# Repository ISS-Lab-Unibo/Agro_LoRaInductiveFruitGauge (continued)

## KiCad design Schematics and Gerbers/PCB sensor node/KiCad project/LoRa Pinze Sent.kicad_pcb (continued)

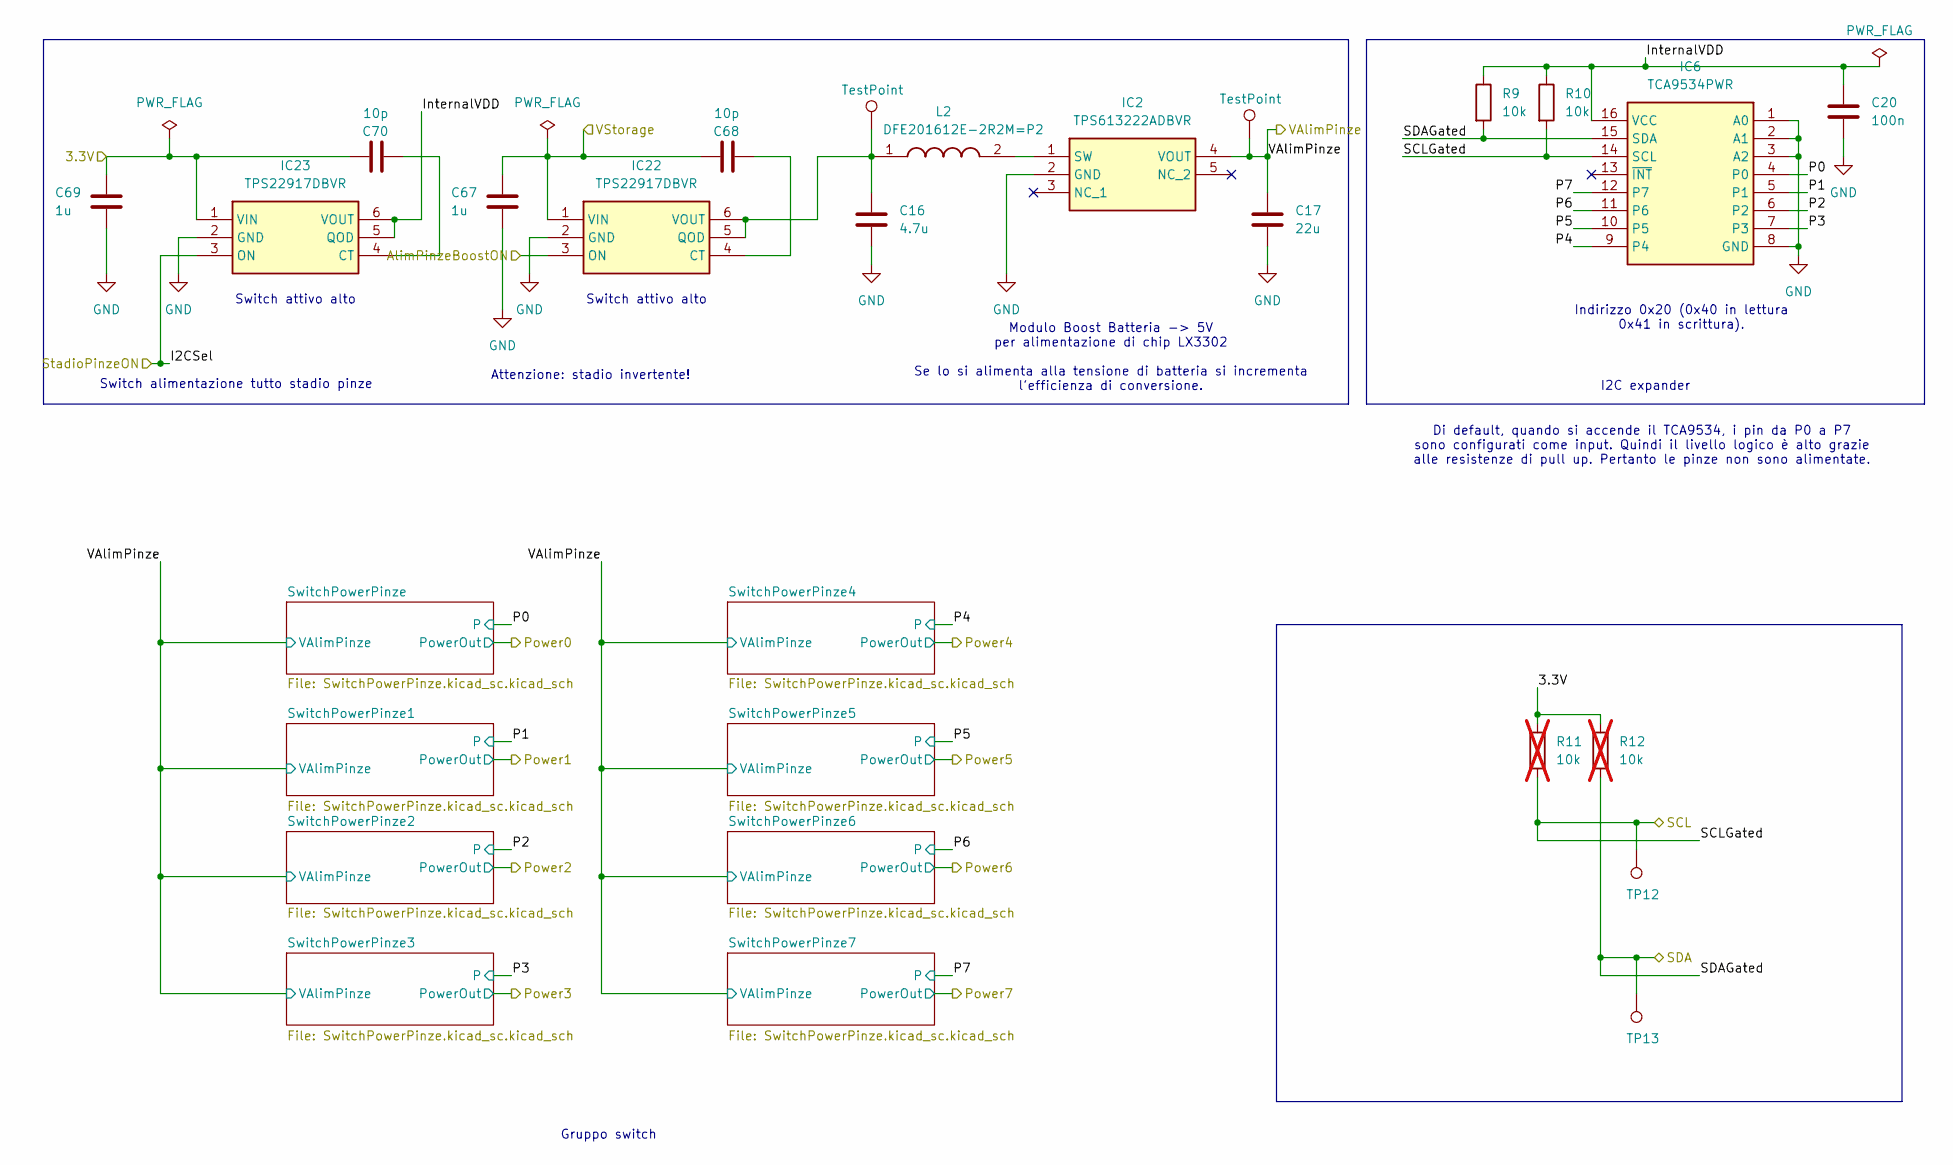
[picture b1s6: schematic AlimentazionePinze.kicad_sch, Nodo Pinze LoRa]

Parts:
C16: 4.7u; C_0402_1005Metric_Pad0.74x0.62mm_HandSolder; LCSC C23733
C17: 22u; C_0805_2012Metric_Pad1.18x1.45mm_HandSolder; LCSC C45783
C20: 100n; C_0402_1005Metric_Pad0.74x0.62mm_HandSolder; LCSC C1525
C67, C69: 1u; C_0402_1005Metric_Pad0.74x0.62mm_HandSolder; LCSC C52923
C68, C70: 10p; C_0402_1005Metric_Pad0.74x0.62mm_HandSolder; LCSC C32949
IC2: TPS613222ADBVR; SOT95P280X145-5N; Manufacturer_Part_Number TPS613222ADBVR; Mouser Part Number 595-TPS613222ADBVR
IC6: TCA9534PWR; SOP65P640X120-16N; Manufacturer_Part_Number TCA9534PWR; Mouser Part Number 595-TCA9534PWR
IC22, IC23: TPS22917DBVR; SOT95P280X145-6N; Manufacturer_Part_Number TPS22917DBVR; Mouser Part Number 595-TPS22917DBVR
L2: DFE201612E-2R2M=P2; 1286ASH1R0MP2; Manufacturer_Part_Number DFE201612E-2R2M=P2; Mouser Part Number 81-DFE201612E-2R2MP2
R9, R10: 10k; R_0402_1005Metric; LCSC C25744
R11, R12: 10k; R_0402_1005Metric; LCSC C25744; not fitted
TP10, TP11, TP12, TP13: TestPoint; TestPoint_Pad_1.0x1.0mm

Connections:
/+5V: C17.1, IC2.4 (VOUT), TP11.1 (1_1); also elsewhere on the board
/AlimentazionePinze/InternalVDD: C20.1, IC6.16 (VCC), IC23.5 (QOD), IC23.6 (VOUT), R9.1, R10.1
/AlimentazionePinze/P0: IC6.4 (P0); also elsewhere on the board
/AlimentazionePinze/P1: IC6.5 (P1); also elsewhere on the board
/AlimentazionePinze/P2: IC6.6 (P2); also elsewhere on the board
/AlimentazionePinze/P3: IC6.7 (P3); also elsewhere on the board
/AlimentazionePinze/P4: IC6.9 (P4); also elsewhere on the board
/AlimentazionePinze/P5: IC6.10 (P5); also elsewhere on the board
/AlimentazionePinze/P6: IC6.11 (P6); also elsewhere on the board
/AlimentazionePinze/P7: IC6.12 (P7); also elsewhere on the board
/BoostOnPinze: IC22.3 (ON); also elsewhere on the board
/I2C1_SCL_PA12: IC6.14 (SCL), R10.2, R11.2, TP12.1 (1_1); also elsewhere on the board
/I2C1_SDA_PA11: IC6.15 (SDA), R9.2, R12.2, TP13.1 (1_1); also elsewhere on the board
/PinzeOn: IC23.3 (ON); also elsewhere on the board
/VBattery: C67.1, C68.1, IC22.1 (VIN); also elsewhere on the board
GND: C16.2, C17.2, C20.2, C67.2, C69.2, IC2.2 (GND), IC6.1 (A0), IC6.2 (A1), IC6.3 (A2), IC6.8 (GND), IC22.2 (GND), IC23.2 (GND); also elsewhere on the board
unnamed: IC2.1 (SW), L2.2
unnamed: C68.2, IC22.4 (CT)
unnamed: C16.1, IC22.5 (QOD), IC22.6 (VOUT), L2.1, TP10.1 (1_1)
unnamed: C70.2, IC23.4 (CT)
VDD_MCU_LRA: C69.1, C70.1, IC23.1 (VIN), R11.1, R12.1; also elsewhere on the board

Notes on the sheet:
Attenzione: stadio invertente!
Modulo Boost Batteria -> 5V per alimentazione di chip LX3302 Se lo si alimenta alla tensione di batteria si incrementa l'efficienza di conversione.
Gruppo switch
Di default, quando si accende il TCA9534, i pin da P0 a P7 sono configurati come input. Quindi il livello logico è alto grazie alle resistenze di pull up. Pertanto le pinze non sono alimentate.
Switch attivo alto
I2C expander
Indirizzo 0x20 (0x40 in lettura 0x41 in scrittura).
Switch alimentazione tutto stadio pinze

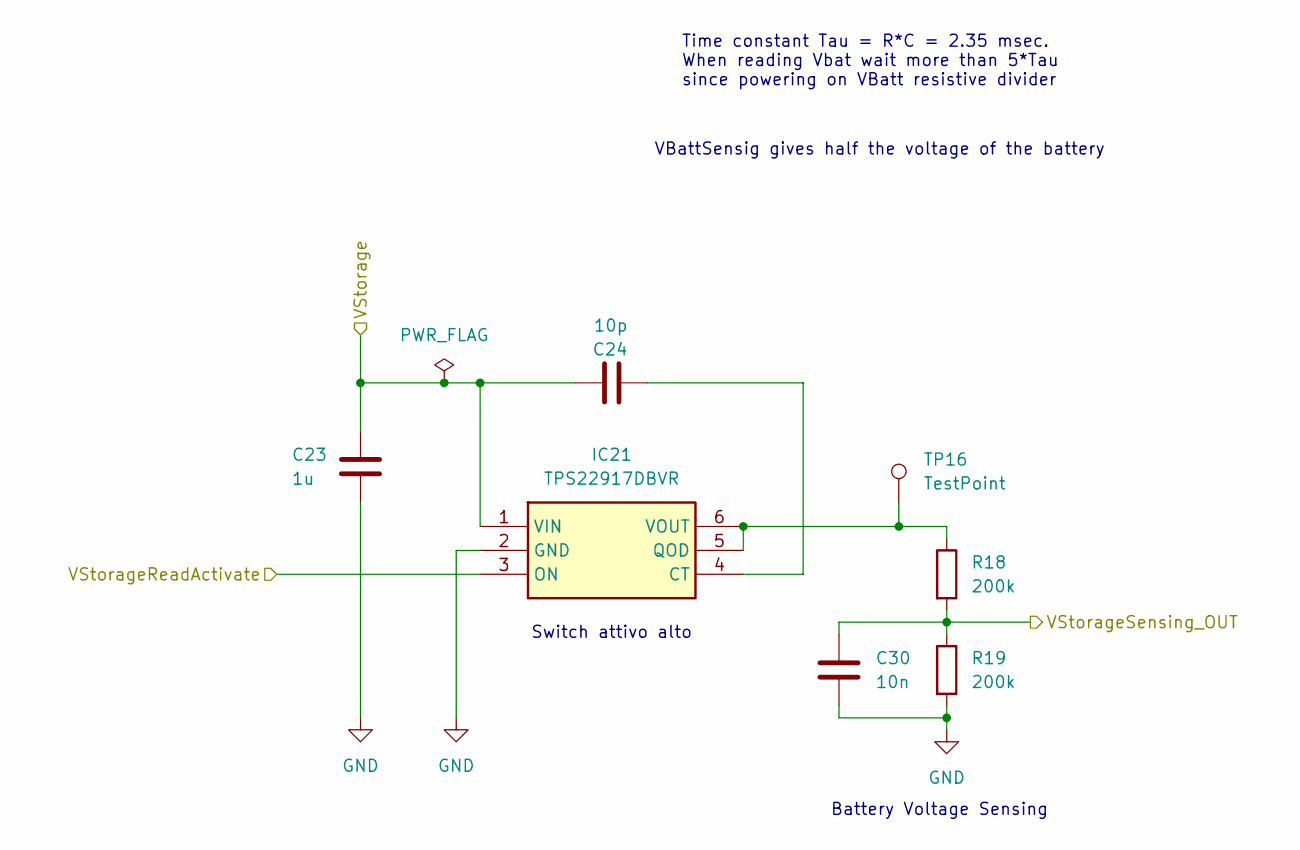
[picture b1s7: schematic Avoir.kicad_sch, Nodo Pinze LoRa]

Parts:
C23: 1u; C_0402_1005Metric_Pad0.74x0.62mm_HandSolder; LCSC C52923
C24: 10p; C_0402_1005Metric_Pad0.74x0.62mm_HandSolder; LCSC C32949
C30: 10n; C_0402_1005Metric_Pad0.74x0.62mm_HandSolder; LCSC C15195
IC21: TPS22917DBVR; SOT95P280X145-6N; Manufacturer_Part_Number TPS22917DBVR; Mouser Part Number 595-TPS22917DBVR
R18, R19: 200k; R_0402_1005Metric; LCSC C25764
TP16: TestPoint; TestPoint_Pad_1.0x1.0mm

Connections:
/VBattery: C23.1, C24.1, IC21.1 (VIN); also elsewhere on the board
/VStorageReadActivate: IC21.3 (ON); also elsewhere on the board
/VStorageSensing: C30.1, R18.2, R19.1; also elsewhere on the board
GND: C23.2, C30.2, IC21.2 (GND), R19.2; also elsewhere on the board
unnamed: C24.2, IC21.4 (CT)
unnamed: IC21.5 (QOD), IC21.6 (VOUT), R18.1, TP16.1 (1_1)

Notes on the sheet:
Time constant Tau = R*C = 2.35 msec. When reading Vbat wait more than 5*Tau since powering on VBatt resistive divider
VBattSensig gives half the voltage of the battery
Switch attivo alto
Battery Voltage Sensing

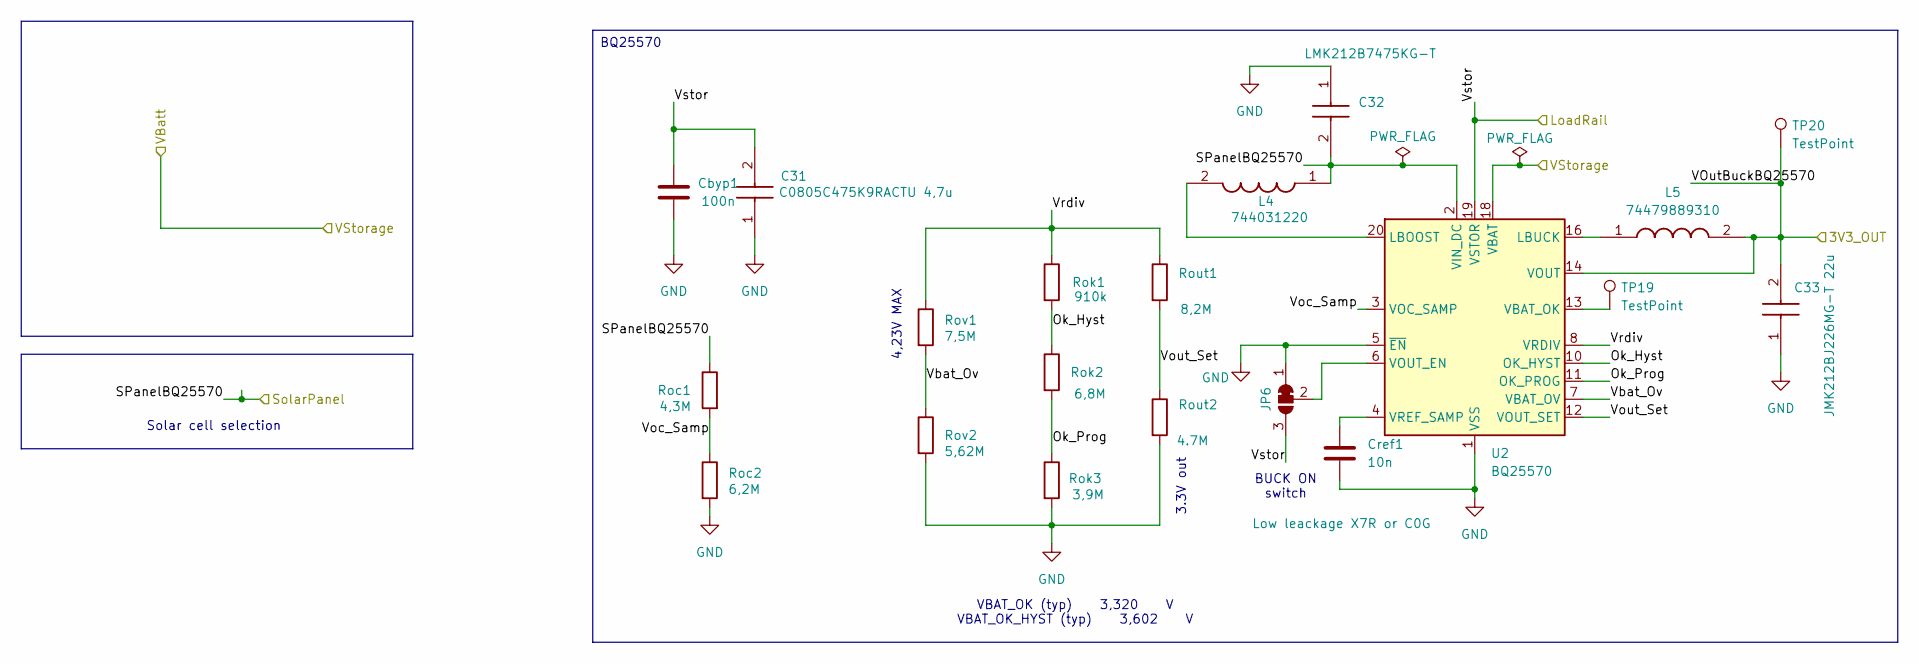
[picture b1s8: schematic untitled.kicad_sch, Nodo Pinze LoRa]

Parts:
C31: C0805C475K9RACTU 4,7u; C0805; Manufacturer_Part_Number C0805C475K9RACTU; Mouser Part Number 80-C0805C475K9R
C32: LMK212B7475KG-T; CAPC2012X135N; Manufacturer_Part_Number LMK212B7475KG-T; Mouser Part Number 963-LMK212B7475KG-T
C33: JMK212BJ226MG-T 22u; CAPC2013X135N; Manufacturer_Part_Number JMK212BJ226MG-T; Mouser Part Number 963-JMK212BJ226MG-T
Cbyp1: 100n; C_0402_1005Metric_Pad0.74x0.62mm_HandSolder; LCSC C1525
Cref1: 10n; C_0402_1005Metric_Pad0.74x0.62mm_HandSolder; LCSC C15195
JP6: SolderJumper_3_Bridged12; SolderJumper-3_P1.3mm_Bridged12_RoundedPad1.0x1.5mm_NumberL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
L4: 744031220; WE-TPC_381692; Manufacturer_Part_Number 744031220; Mouser Part Number 710-744031220
L5: 74479889310; INDC2521X120N; Manufacturer_Part_Number 74479889310; LCSC C191565
Roc1: 4,3M; R_0402_1005Metric_Pad0.72x0.64mm_HandSolder; LCSC C327242
Roc2: 6,2M; R_0402_1005Metric_Pad0.72x0.64mm_HandSolder; LCSC C159000
Rok1: 910k; R_0402_1005Metric_Pad0.72x0.64mm_HandSolder; LCSC C324817
Rok2: 6,8M; R_0402_1005Metric_Pad0.72x0.64mm_HandSolder; LCSC C620473
Rok3: 3,9M; R_0402_1005Metric_Pad0.72x0.64mm_HandSolder; LCSC C30329
Rout1: 8,2M; R_0402_1005Metric_Pad0.72x0.64mm_HandSolder; LCSC C172186
Rout2: 4.7M; R_0402_1005Metric_Pad0.72x0.64mm_HandSolder; LCSC C49654986
Rov1: 7,5M; R_0402_1005Metric_Pad0.72x0.64mm_HandSolder; LCSC C137839
Rov2: 5,62M; R_0402_1005Metric_Pad0.72x0.64mm_HandSolder; LCSC C2929925
TP19, TP20: TestPoint; TestPoint_Pad_1.0x1.0mm
U2: BQ25570; QFN-20-1EP_3.5x3.5mm_P0.5mm_EP2x2mm; LCSC C506250

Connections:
/LoadRail: C31.2, Cbyp1.2, JP6.3 (B), U2.19 (VSTOR)
/SolarPanel: C32.2, L4.1, Roc1.1, U2.2 (VIN_DC); also elsewhere on the board
/VBattery: U2.18 (VBAT); also elsewhere on the board
/power_supply1/Ok_Hyst: Rok1.2, Rok2.1, U2.10 (OK_HYST)
/power_supply1/Ok_Prog: Rok2.2, Rok3.1, U2.11 (OK_PROG)
/power_supply1/Vbat_Ov: Rov1.2, Rov2.1, U2.7 (VBAT_OV)
/power_supply1/Voc_Samp: Roc1.2, Roc2.1, U2.3 (VOC_SAMP)
/power_supply1/Vout_Set: Rout1.2, Rout2.1, U2.12 (VOUT_SET)
/power_supply1/Vrdiv: Rok1.1, Rout1.1, Rov1.1, U2.8 (VRDIV)
GND: C31.1, C32.1, C33.1, Cbyp1.1, Cref1.1, JP6.1 (A), Roc2.2, Rok3.2, Rout2.2, Rov2.2, U2.1 (VSS), U2.5 (~EN), U2.9 (VSS), U2.15 (VSS), U2.17 (VSS), U2.21 (VSS); also elsewhere on the board
unnamed: JP6.2 (C), U2.6 (VOUT_EN)
unnamed: L4.2, U2.20 (LBOOST)
unnamed: L5.1, U2.16 (LBUCK)
unnamed: TP19.1 (1_1), U2.13 (VBAT_OK)
unnamed: Cref1.2, U2.4 (VREF_SAMP)
VDD_MCU_LRA: C33.2, L5.2, TP20.1 (1_1), U2.14 (VOUT); also elsewhere on the board

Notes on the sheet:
BUCK ON switch
3.3V out
4,23V MAX
Solar cell selection
VBAT_OK (typ) 3,320 V VBAT_OK_HYST (typ) 3,602 V
BQ25570

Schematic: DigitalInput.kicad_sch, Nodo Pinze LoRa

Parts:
D21, D29: BAV199; SOT95P230X100-3N; Manufacturer_Part_Number BAV199; Mouser Part Number N/A
J9: 53398-0471; 533980471; Manufacturer_Part_Number 53398-0471; Mouser Part Number 538-53398-0471
R47, R49: 12k; R_0402_1005Metric; LCSC C25752
R48, R50: 22k; R_0402_1005Metric; LCSC C25768

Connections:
/+5V: D21.2 (CATHODE), D29.2 (CATHODE); also elsewhere on the board
/AlimentazionePinze/Power0: J9.4; also elsewhere on the board
/DigitalInputMux/D0: R47.1, R48.2; also elsewhere on the board
/DigitalInputMux/DigitalInput/IND: D21.3 (COMMON), J9.3, R47.2
/DigitalInputMux/DigitalInput/INT: D29.3 (COMMON), J9.2, R49.2
/DigitalInputMux/T0: R49.1, R50.2; also elsewhere on the board
GND: D21.1 (ANODE), D29.1 (ANODE), J9.1, R48.1, R50.1; also elsewhere on the board

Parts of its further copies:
D22, D23, D24, D25, D26, D27, D28, D30, D31, D32, D33, D34, D35, D36: BAV199; SOT95P230X100-3N; Manufacturer_Part_Number BAV199; Mouser Part Number N/A
J10, J11, J12, J13, J14, J15, J16: 53398-0471; 533980471; Manufacturer_Part_Number 53398-0471; Mouser Part Number 538-53398-0471
R51, R53, R55, R57, R59, R61, R63, R65, R67, R69, R71, R73, R75, R77: 12k; R_0402_1005Metric; LCSC C25752
R52, R54, R56, R58, R60, R62, R64, R66, R68, R70, R72, R74, R76, R78: 22k; R_0402_1005Metric; LCSC C25768

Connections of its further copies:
/+5V: D22.2 (CATHODE), D23.2 (CATHODE), D24.2 (CATHODE), D25.2 (CATHODE), D26.2 (CATHODE), D27.2 (CATHODE), D28.2 (CATHODE), D30.2 (CATHODE), D31.2 (CATHODE), D32.2 (CATHODE), D33.2 (CATHODE), D34.2 (CATHODE), D35.2 (CATHODE), D36.2 (CATHODE); also elsewhere on the board
/AlimentazionePinze/Power1: J10.4; also elsewhere on the board
/AlimentazionePinze/Power2: J11.4; also elsewhere on the board
/AlimentazionePinze/Power3: J12.4; also elsewhere on the board
/AlimentazionePinze/Power4: J13.4; also elsewhere on the board
/AlimentazionePinze/Power5: J14.4; also elsewhere on the board
/AlimentazionePinze/Power6: J15.4; also elsewhere on the board
/AlimentazionePinze/Power7: J16.4; also elsewhere on the board
/DigitalInputMux/D1: R51.1, R52.2; also elsewhere on the board
/DigitalInputMux/D2: R55.1, R56.2; also elsewhere on the board
/DigitalInputMux/D3: R59.1, R60.2; also elsewhere on the board
/DigitalInputMux/D4: R63.1, R64.2; also elsewhere on the board
/DigitalInputMux/D5: R67.1, R68.2; also elsewhere on the board
/DigitalInputMux/D6: R71.1, R72.2; also elsewhere on the board
/DigitalInputMux/D7: R75.1, R76.2; also elsewhere on the board
/DigitalInputMux/DigitalInput1/IND: D22.3 (COMMON), J10.3, R51.2
/DigitalInputMux/DigitalInput1/INT: D30.3 (COMMON), J10.2, R53.2
/DigitalInputMux/DigitalInput2/IND: D23.3 (COMMON), J11.3, R55.2
/DigitalInputMux/DigitalInput2/INT: D31.3 (COMMON), J11.2, R57.2
/DigitalInputMux/DigitalInput3/IND: D24.3 (COMMON), J12.3, R59.2
/DigitalInputMux/DigitalInput3/INT: D32.3 (COMMON), J12.2, R61.2
/DigitalInputMux/DigitalInput4/IND: D25.3 (COMMON), J13.3, R63.2
/DigitalInputMux/DigitalInput4/INT: D33.3 (COMMON), J13.2, R65.2
/DigitalInputMux/DigitalInput5/IND: D26.3 (COMMON), J14.3, R67.2
/DigitalInputMux/DigitalInput5/INT: D34.3 (COMMON), J14.2, R69.2
/DigitalInputMux/DigitalInput6/IND: D27.3 (COMMON), J15.3, R71.2
/DigitalInputMux/DigitalInput6/INT: D35.3 (COMMON), J15.2, R73.2
/DigitalInputMux/DigitalInput7/IND: D28.3 (COMMON), J16.3, R75.2
/DigitalInputMux/DigitalInput7/INT: D36.3 (COMMON), J16.2, R77.2
/DigitalInputMux/T1: R53.1, R54.2; also elsewhere on the board
/DigitalInputMux/T2: R57.1, R58.2; also elsewhere on the board
/DigitalInputMux/T3: R61.1, R62.2; also elsewhere on the board
/DigitalInputMux/T4: R65.1, R66.2; also elsewhere on the board
/DigitalInputMux/T5: R69.1, R70.2; also elsewhere on the board
/DigitalInputMux/T6: R73.1, R74.2; also elsewhere on the board
/DigitalInputMux/T7: R77.1, R78.2; also elsewhere on the board
GND: D22.1 (ANODE), D23.1 (ANODE), D24.1 (ANODE), D25.1 (ANODE), D26.1 (ANODE), D27.1 (ANODE), D28.1 (ANODE), D30.1 (ANODE), D31.1 (ANODE), D32.1 (ANODE), D33.1 (ANODE), D34.1 (ANODE), D35.1 (ANODE), D36.1 (ANODE), J10.1, J11.1, J12.1, J13.1, J14.1, J15.1, J16.1, R52.1, R54.1, R56.1, R58.1, R60.1, R62.1, R64.1, R66.1, R68.1, R70.1, R72.1, R74.1, R76.1, R78.1; also elsewhere on the board

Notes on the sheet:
Partitore resisttivo: entrano 5V, escono 3.23V

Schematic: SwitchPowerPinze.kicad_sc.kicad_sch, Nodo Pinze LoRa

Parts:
C43, C45: 1u; C_0402_1005Metric_Pad0.74x0.62mm_HandSolder; LCSC C52923
C44: 10p; C_0402_1005Metric_Pad0.74x0.62mm_HandSolder; LCSC C32949
IC13: TPS22917DBVR; SOT95P280X145-6N; Manufacturer_Part_Number TPS22917DBVR; Mouser Part Number 595-TPS22917DBVR

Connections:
/+5V: C43.1, C44.1, IC13.1 (VIN); also elsewhere on the board
/AlimentazionePinze/P0: IC13.3 (ON); also elsewhere on the board
/AlimentazionePinze/Power0: C45.1, IC13.5 (QOD), IC13.6 (VOUT); also elsewhere on the board
GND: C43.2, C45.2, IC13.2 (GND); also elsewhere on the board
unnamed: C44.2, IC13.4 (CT)

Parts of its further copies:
C46, C48, C49, C50, C52, C54, C55, C57, C58, C60, C61, C63, C64, C66, C71, C73: 1u; C_0402_1005Metric_Pad0.74x0.62mm_HandSolder; LCSC C52923
C47, C51, C53, C56, C59, C62, C65, C72: 10p; C_0402_1005Metric_Pad0.74x0.62mm_HandSolder; LCSC C32949
IC14, IC15, IC16, IC17, IC18, IC19, IC20, IC24: TPS22917DBVR; SOT95P280X145-6N; Manufacturer_Part_Number TPS22917DBVR; Mouser Part Number 595-TPS22917DBVR

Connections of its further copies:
/+5V: C46.1, C47.1, C49.1, C50.1, C51.1, C53.1, C55.1, C56.1, C58.1, C59.1, C61.1, C62.1, C64.1, C65.1, IC14.1 (VIN), IC15.1 (VIN), IC16.1 (VIN), IC17.1 (VIN), IC18.1 (VIN), IC19.1 (VIN), IC20.1 (VIN); also elsewhere on the board
/AlimentazionePinze/P1: IC14.3 (ON); also elsewhere on the board
/AlimentazionePinze/P2: IC15.3 (ON); also elsewhere on the board
/AlimentazionePinze/P3: IC16.3 (ON); also elsewhere on the board
/AlimentazionePinze/P4: IC17.3 (ON); also elsewhere on the board
/AlimentazionePinze/P5: IC18.3 (ON); also elsewhere on the board
/AlimentazionePinze/P6: IC19.3 (ON); also elsewhere on the board
/AlimentazionePinze/P7: IC20.3 (ON); also elsewhere on the board
/AlimentazionePinze/Power1: C48.1, IC14.5 (QOD), IC14.6 (VOUT); also elsewhere on the board
/AlimentazionePinze/Power2: C54.1, IC15.5 (QOD), IC15.6 (VOUT); also elsewhere on the board
/AlimentazionePinze/Power3: C57.1, IC16.5 (QOD), IC16.6 (VOUT); also elsewhere on the board
/AlimentazionePinze/Power4: C60.1, IC17.5 (QOD), IC17.6 (VOUT); also elsewhere on the board
/AlimentazionePinze/Power5: C63.1, IC18.5 (QOD), IC18.6 (VOUT); also elsewhere on the board
/AlimentazionePinze/Power6: C66.1, IC19.5 (QOD), IC19.6 (VOUT); also elsewhere on the board
/AlimentazionePinze/Power7: C52.1, IC20.5 (QOD), IC20.6 (VOUT); also elsewhere on the board
/AnalogPowerIN: IC24.3 (ON); also elsewhere on the board
/InputAnalogico/AnalogSupply: C73.1, IC24.5 (QOD), IC24.6 (VOUT); also elsewhere on the board
GND: C46.2, C48.2, C49.2, C50.2, C52.2, C54.2, C55.2, C57.2, C58.2, C60.2, C61.2, C63.2, C64.2, C66.2, C71.2, C73.2, IC14.2 (GND), IC15.2 (GND), IC16.2 (GND), IC17.2 (GND), IC18.2 (GND), IC19.2 (GND), IC20.2 (GND), IC24.2 (GND); also elsewhere on the board
unnamed: C47.2, IC14.4 (CT)
unnamed: C53.2, IC15.4 (CT)
unnamed: C56.2, IC16.4 (CT)
unnamed: C59.2, IC17.4 (CT)
unnamed: C62.2, IC18.4 (CT)
unnamed: C65.2, IC19.4 (CT)
unnamed: C51.2, IC20.4 (CT)
unnamed: C72.2, IC24.4 (CT)
VDD_MCU_LRA: C71.1, C72.1, IC24.1 (VIN); also elsewhere on the board

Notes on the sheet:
Switch attivo alto

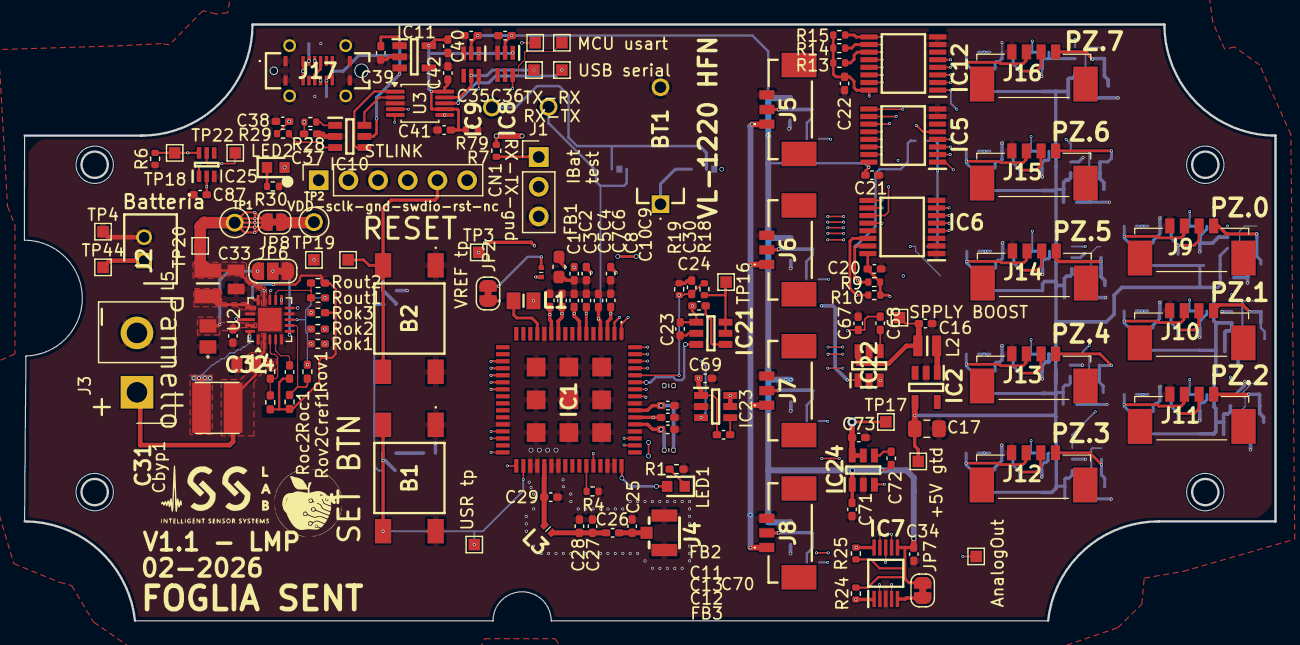
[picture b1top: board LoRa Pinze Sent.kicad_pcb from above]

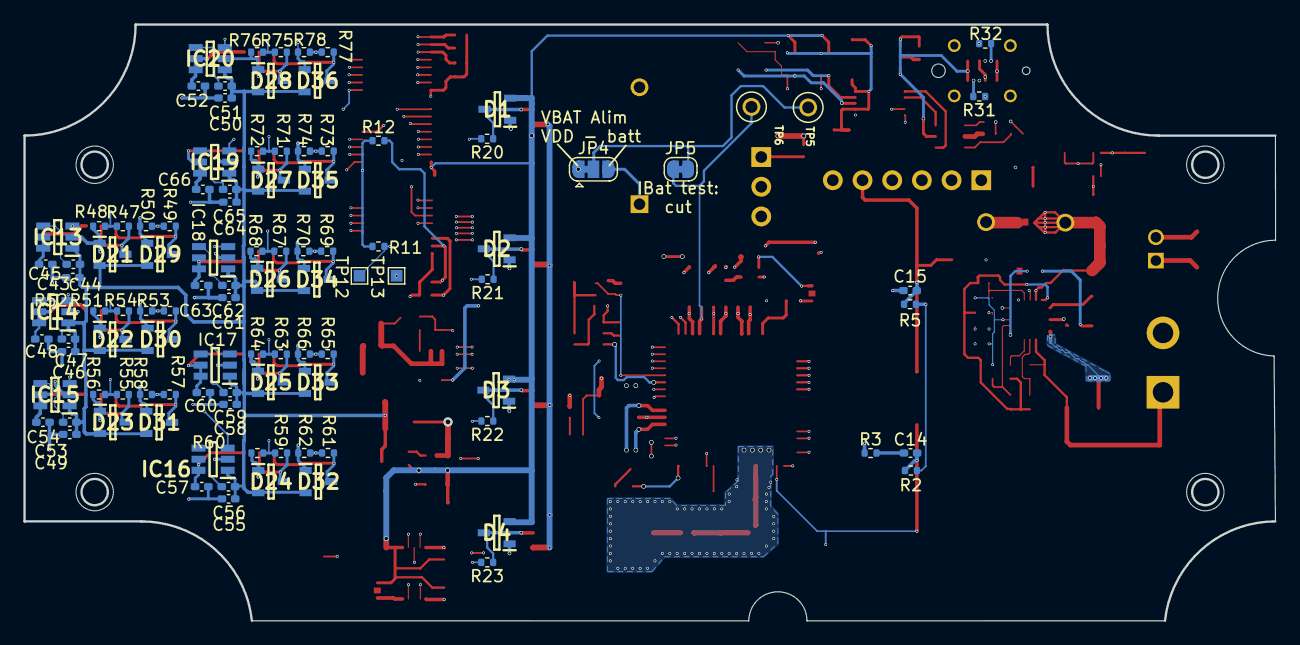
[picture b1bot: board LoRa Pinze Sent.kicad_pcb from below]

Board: 6 copper layers, 107.0 x 51.0 mm, 253 parts (103 on the bottom side), 146 nets.

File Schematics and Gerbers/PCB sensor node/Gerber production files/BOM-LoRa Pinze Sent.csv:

Comment,Designator,Footprint,LCSC,Quantity
0.47u,C2,C_0603_1608Metric_Pad1.08x0.95mm_HandSolder,C1623,1
10,"R20,R21,R22,R23",R_0402_1005Metric,C25077,4
100k,"R13,R14,R15,R24,R25",R_0402_1005Metric,C25741,5
100n,"C1,C10,C11,C15,C20,C21,C22,C3,C34,C35,C36,C41,C42,C5,C7,C87,Cbyp1",C_0402_1005Metric_Pad0.74x0.62mm_HandSolder,C1525,17
100p,C26,C_0402_1005Metric_Pad0.74x0.62mm_HandSolder,C1546,1
10k,"R10,R4,R5,R9",R_0402_1005Metric,C25744,4
10n,"C30,Cref1",C_0402_1005Metric_Pad0.74x0.62mm_HandSolder,C15195,2
10p,"C24,C37,C38,C44,C47,C51,C53,C56,C59,C62,C65,C68,C70,C72",C_0402_1005Metric_Pad0.74x0.62mm_HandSolder,C32949,14
12k,"R47,R49,R51,R53,R55,R57,R59,R61,R63,R65,R67,R69,R71,R73,R75,R77",R_0402_1005Metric,C25752,16
1k,R79,R_0402_1005Metric,C11702,1
1u,"C12,C13,C23,C39,C4,C40,C43,C45,C46,C48,C49,C50,C52,C54,C55,C57,C58,C60,C61,C63,C64,C66,C67,C69,C71,C73,C8",C_0402_1005Metric_Pad0.74x0.62mm_HandSolder,C52923,27
200k,"R18,R19",R_0402_1005Metric,C25764,2
220,"R1,R30",R_0402_1005Metric_Pad0.72x0.64mm_HandSolder,C25091,2
22k,"R48,R50,R52,R54,R56,R58,R60,R62,R64,R66,R68,R70,R72,R74,R76,R78",R_0402_1005Metric,C25768,16
22u,C17,C_0805_2012Metric_Pad1.18x1.45mm_HandSolder,C45783,1
2k2,"R6,R7",R_0402_1005Metric,C25879,2
"3,9M",Rok3,R_0402_1005Metric_Pad0.72x0.64mm_HandSolder,C30329,1
3.3p,"C28,C29",C_0402_1005Metric_Pad0.74x0.62mm_HandSolder,C1565,2
33,"R28,R29",R_0402_1005Metric,C25105,2
"4,3M",Roc1,R_0402_1005Metric_Pad0.72x0.64mm_HandSolder,C327242,1
4.7M,Rout2,R_0402_1005Metric_Pad0.72x0.64mm_HandSolder,C49654986,1
4.7u,C16,C_0402_1005Metric_Pad0.74x0.62mm_HandSolder,C23733,1
4u7,"C6,C9",C_0402_1005Metric_Pad0.74x0.62mm_HandSolder,C23733,2
"5,62M",Rov2,R_0402_1005Metric_Pad0.72x0.64mm_HandSolder,C2929925,1
53398-0371,"J5,J6,J7,J8",533980371,C17246903,4
53398-0471,"J10,J11,J12,J13,J14,J15,J16,J9",533980471,C17617036,8
56k,"R31,R32",R_0402_1005Metric,C23206,2
"6,2M",Roc2,R_0402_1005Metric_Pad0.72x0.64mm_HandSolder,C159000,1
"6,8M",Rok2,R_0402_1005Metric_Pad0.72x0.64mm_HandSolder,C620473,1
"7,5M",Rov1,R_0402_1005Metric_Pad0.72x0.64mm_HandSolder,C137839,1
744031220,L4,WE-TPC_381692,C5523436,1
74479889310,L5,INDC2521X120N,C191565,1
"8,2M",Rout1,R_0402_1005Metric_Pad0.72x0.64mm_HandSolder,C172186,1
910k,Rok1,R_0402_1005Metric_Pad0.72x0.64mm_HandSolder,C324817,1
BAV199,"D1,D2,D21,D22,D23,D24,D25,D26,D27,D28,D29,D3,D30,D31,D32,D33,D34,D35,D36,D4",SOT95P230X100-3N,C145516,20
BLM15HG102SN1D,"FB1,FB2,FB3",NFZ15SG152SN10B,C76889,3
BQ25570,U2,QFN-20-1EP_3.5x3.5mm_P0.5mm_EP2x2mm,C506250,1
"C0805C475K9RACTU 4,7u",C31,C0805,C1779,1
CH340E,U3,MSOP-10_3x3mm_P0.5mm,C99652,1
DFE201612E-2R2M=P2,L2,1286ASH1R0MP2,C337893,1
GT-USB-7055BB,J17,GTUSB7055BB,C7450621,1
JMK212BJ226MG-T 22u,C33,CAPC2013X135N,C87158,1
KT-0603R,"LED1,LED2",LEDC1608X70N,C2286,2
LMK212B7475KG-T,C32,CAPC2012X135N,C92810,1
LQW15AN8N2J00D,L3,LQW15CNR20J00B,C98066,1
MLZ2012N150LT000,L1,INDC2012X105N,C531290,1
NCP115ASN330T2G,IC11,SOT95P275X110-5N,C603505,1
RAK3172-SiP,IC1,RAK3172SiP,C19818882,1
Reset(Black),B2,TS046655BK160SMT,C5340119,1
SN74HCS151PWR,"IC12,IC5",SOP65P640X120-16N,C2877065,2
TCA9534PWR,IC6,SOP65P640X120-16N,C783615,1
TMUX1204DGSR,IC7,SOP50P490X110-10N,C2840022,1
TMUX1219DCKR,"IC25,IC8,IC9",SOT65P210X110-6N,C2867958,3
TPS22917DBVR,"IC13,IC14,IC15,IC16,IC17,IC18,IC19,IC20,IC21,IC22,IC23,IC24",SOT95P280X145-6N,C2681320,12
TPS613222ADBVR,IC2,SOT95P280X145-5N,C2071163,1
U.FL-R-SMT-1_10_,J4,U.FL-R-SMT-1_10_,C88374,1
USBLC6-2SC6,IC10,SOT95P280X145-6N,C2827654,1

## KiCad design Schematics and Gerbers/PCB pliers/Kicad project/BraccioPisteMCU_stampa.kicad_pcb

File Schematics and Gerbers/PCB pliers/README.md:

# Fruit Gauge (Pliers) PCBs

Design and production files of the inductive fruit gauge.

| Folder / file | Contents |
| ------------- | -------- |
| `Kicad project/` | KiCad 10 project `BraccioPisteMCU_stampa` (schematic + layout of all gauge boards) |
| `BraccioPisteMCU_stampa_schematic.pdf` | PDF schematic |
| `gerber production files/` | Gerbers, BOM and CPL of the four boards |

## Working principle

The gauge is a caliper with two arms joined at a pivot. A fruit held between the clips sets the opening angle α of the arms. The diameter is then:

```
d = 2 · L · sin(α / 2) − 2 · L_clip
```

where *L* is the arm length and *L_clip* the length of the PETG clips. Both lengths are corrected for thermal expansion using the on-board temperature sensor.

The angle is measured without any contact by an **inductive position sensor**. The sensing arm carries one transmitting coil and two receiving coils, printed on the PCB. The other arm carries a copper target. The TX coil, resonating at about 4.2 MHz, induces eddy currents in the target. The RX coils, laid out in phase opposition, pick up a signal whose envelope depends on the target position. The Microchip LX3302A drives the coils, demodulates the signal and outputs the position over **SENT**.

| Parameter | Value |
| --------- | ----- |
| Resolution | 71 µm (1 LSB, after averaging N = 40 at 2 kS/s) |
| Range | up to 120 mm |
| Accuracy (cubic-spline calibration, 33 points) | MAE 111 µm, max 247 µm |
| TX coils | L ≈ 2.06 / 2.47 µH, Q ≈ 17 / 15, tuned with 680 pF |
| Coil traces | 0.127 mm width, 0.15 mm clearance, inner radius 10 mm, outer diameter 28 mm |
| Target | 60° copper sector between Ø 9.8 mm and Ø 28 mm on both layers |

Temperature tests from −10 °C to 60 °C showed a drift of no more than 1 LSB for the IC and none measurable for the coils. The main thermal effect is the expansion of the arms and clips, which the node compensates for.

## Boards

| Board | Gerber | Description | Assembled |
| ----- | ------ | ----------- | --------- |
| **Piste** | `GERBER-Piste.zip` | Sensing arm: TX/RX coils, LX3302A, LMT01, MCP6541, cable and programming pads | **Yes** (`BOM-Piste.csv`, `CPL-Piste.csv`) |
| **Braccio** | `GERBER-Braccio.zip` | Second arm | No |
| **TargetGrande** | `GERBER-TargetGrande.zip` | Inductive target | No |
| **spacer** | `GERBER-spacer.zip` | FR4 spacer | No |

All boards are 2-layer FR4, 1.6 mm thick. The FR4 is also the structural material of the gauge.

## Schematic (Piste board)

| Ref | Part | Function |
| --- | ---- | -------- |
| IC1 | LX3302AQPW | Inductive sensor interface. IO1 = PWM, IO2 = SENT, IO3 = analog out, each with a 10 k pull-up to VIN |
| C4, C5 | 680 pF | TX LC tank capacitors |
| U1 | LMT01 | Temperature sensor with pulse-count current output |
| IC2 | MCP6541 | Comparator that turns the LMT01 current pulses (across a 10 k resistor) into logic pulses. Threshold 0.76 V, set by a 56k/10k divider from VIN |
| C1–C3, C6, C7 | | Decoupling |

Supply: VIN = 5 V from the node, switched on only during readings.

### Pads

| Group | Pad | Signal |
| ----- | --- | ------ |
| Cable to node | J3 | VIN (+5 V) |
| | J2 | GND |
| | J4 | SENT |
| | J5 | Temperature (LMT01 pulses) |
| LX3302A programming | J1 | VIN |
| | J9 | GND |
| | J8 | IO1 (PWM) |
| | J7 | IO2 (SENT) |
| | J6 | IO3 (analog) |

The LX3302A EEPROM is programmed with the Microchip LXM9518 and [`Firmware/lx3302a_config.txt`](../../Firmware/lx3302a_config.txt). See the [building instructions](../../building_instructions.md#4-lx3302a-programming).

## Manufacturing

Order one set of the four boards for each gauge. Only **Piste** needs assembly. The LMT01 has no LCSC code in the BOM and may have to be sourced and soldered separately.

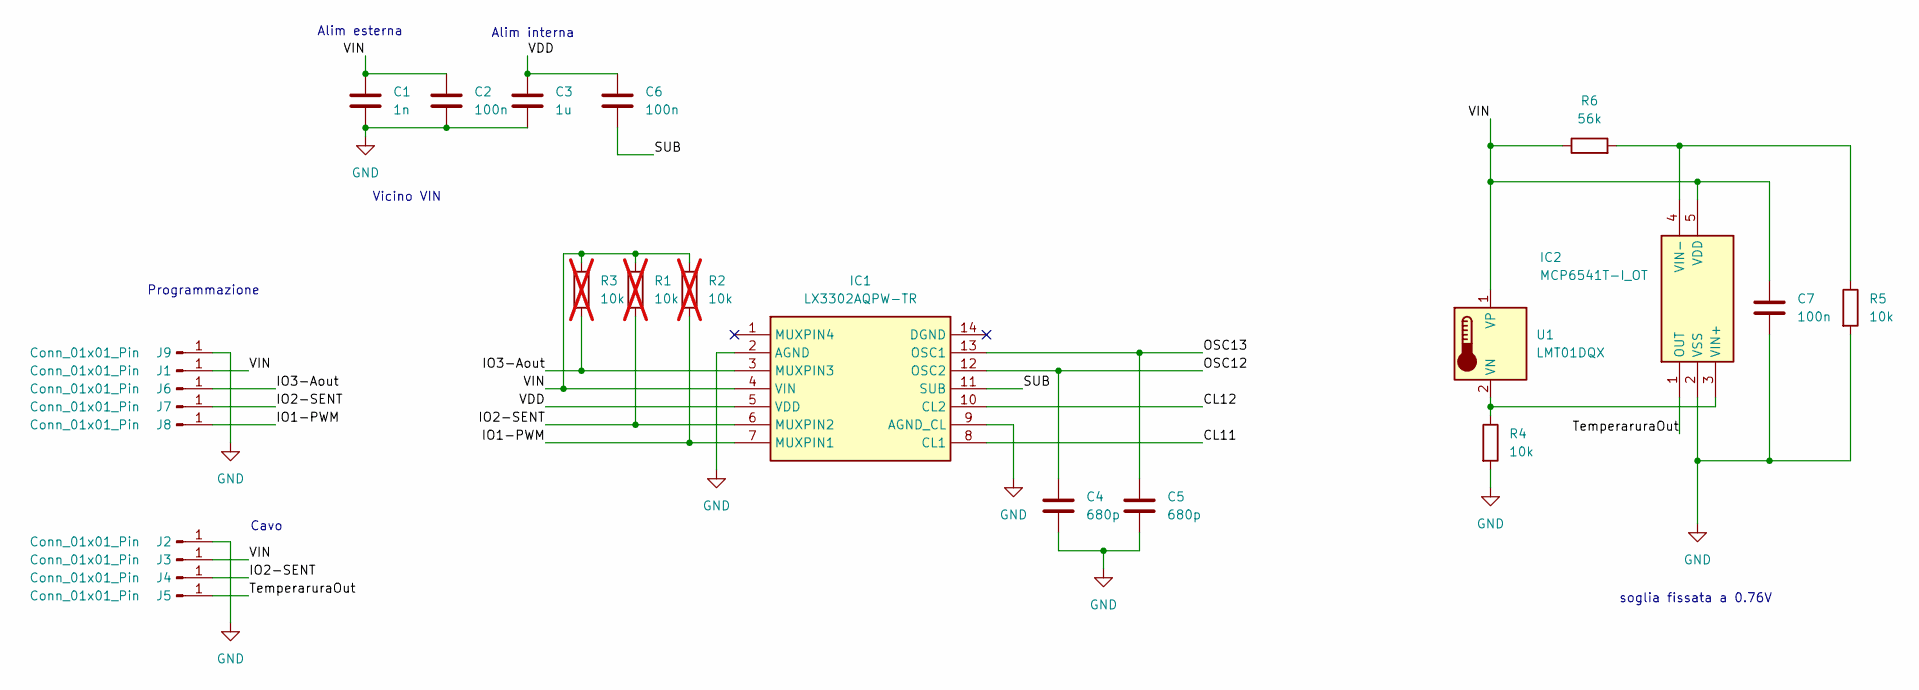
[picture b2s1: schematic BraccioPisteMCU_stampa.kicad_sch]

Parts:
C1: 1n; C_0402_1005Metric_Pad0.74x0.62mm_HandSolder
C2, C6, C7: 100n; C_0402_1005Metric_Pad0.74x0.62mm_HandSolder
C3: 1u; C_0402_1005Metric_Pad0.74x0.62mm_HandSolder
C4, C5: 680p; C_0402_1005Metric_Pad0.74x0.62mm_HandSolder
IC1: LX3302AQPW-TR; SOP65P640X120-14N; Manufacturer_Part_Number LX3302AQPW-TR; Mouser Part Number 494-LX3302AQPW-TR
IC2: MCP6541T-I_OT; SOT95P270X145-5N; Manufacturer_Part_Number MCP6541T-I/OT; Mouser Part Number 579-MCP6541T-I/OT
J1, J2, J3, J4, J5, J6, J7, J8, J9: Conn_01x01_Pin; SolderWirePad_1x01_SMD_1x2mm
R1, R2, R3: 10k; R_0402_1005Metric_Pad0.72x0.64mm_HandSolder; not fitted
R4, R5: 10k; R_0402_1005Metric_Pad0.72x0.64mm_HandSolder
R6: 56k; R_0402_1005Metric_Pad0.72x0.64mm_HandSolder
U1: LMT01DQX; Texas_DQX002A

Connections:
/CL11: IC1.8 (CL1)
/CL12: IC1.10 (CL2)
/IO1-PWM: IC1.7 (MUXPIN1), J8.1 (Pin_1_1), R2.2
/IO2-SENT: IC1.6 (MUXPIN2), J4.1 (Pin_1_1), J7.1 (Pin_1_1), R1.2
/IO3-Aout: IC1.3 (MUXPIN3), J6.1 (Pin_1_1), R3.2
/OSC12: C4.1, IC1.12 (OSC2)
/OSC13: C5.1, IC1.13 (OSC1)
/SUB: C6.2, IC1.11 (SUB)
/TemperaruraOut: IC2.1 (OUT), J5.1 (Pin_1_1)
/VDD: C3.1, C6.1, IC1.5 (VDD)
/VIN: C1.1, C2.1, C7.1, IC1.4 (VIN), IC2.5 (VDD), J1.1 (Pin_1_1), J3.1 (Pin_1_1), R1.1, R2.1, R3.1, R6.1, U1.1 (VP)
GND: C1.2, C2.2, C3.2, C4.2, C5.2, C7.2, IC1.2 (AGND), IC1.9 (AGND_CL), IC2.2 (VSS), J2.1 (Pin_1_1), J9.1 (Pin_1_1), R4.2, R5.2
unnamed: IC2.3 (VIN+), R4.1, U1.2 (VN)
unnamed: IC2.4 (VIN-), R5.1, R6.2

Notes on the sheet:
Vicino VIN
soglia fissata a 0.76V
Cavo
Alim esterna
Alim interna
Programmazione

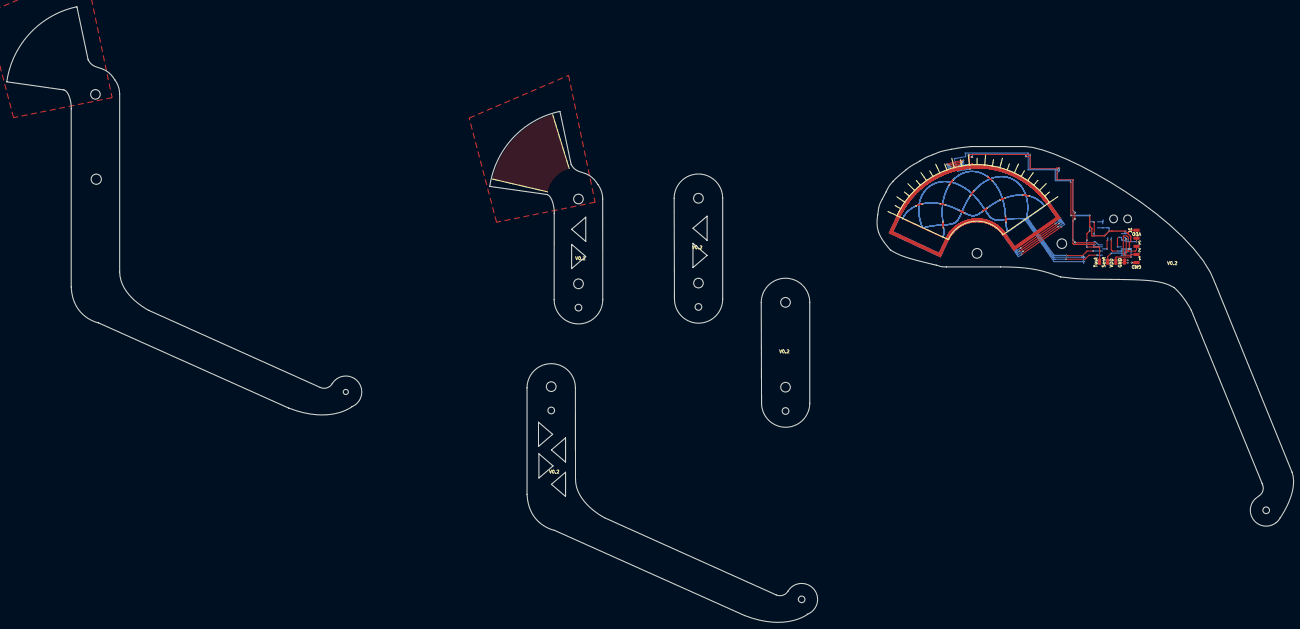
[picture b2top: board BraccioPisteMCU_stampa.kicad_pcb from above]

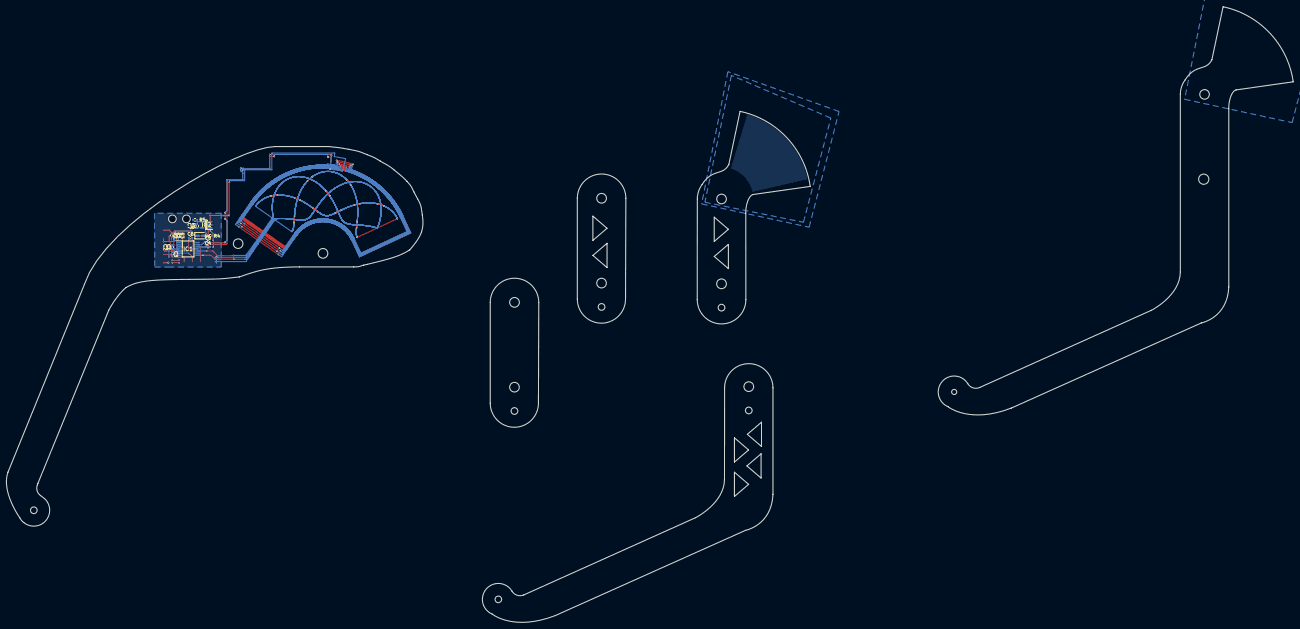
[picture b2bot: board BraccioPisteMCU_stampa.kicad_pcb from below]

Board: 2 copper layers, 130.8 x 119.2 mm, 25 parts (16 on the bottom side), 12 nets.

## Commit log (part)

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2026-05-31 python interface, exe file and 3D cad files
2026-05-31 Rename NOTE.md to README.md
2026-06-01 Added schematics and KiCad files
2026-06-01 Updated GUI
2026-06-02 Added Chirpstack decoder, updated battery reading
2026-06-02 changed JS
2026-06-08 updated 3d models folder
2026-06-08 update instructions
2026-06-08 updated instructions
2026-06-08 LX3320A FW added
2026-06-15 .nc teflon disks files addes
